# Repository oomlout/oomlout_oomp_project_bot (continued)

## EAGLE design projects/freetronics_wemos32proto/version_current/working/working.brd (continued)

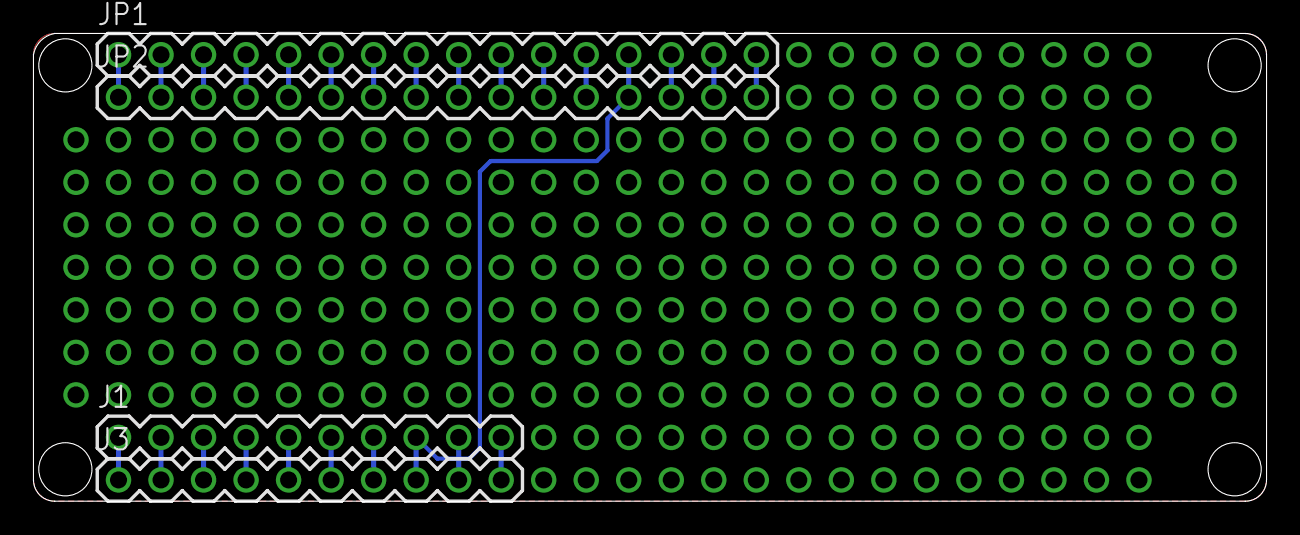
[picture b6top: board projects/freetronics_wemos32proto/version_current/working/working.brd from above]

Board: 2 copper layers, 73.7 x 27.9 mm, 4 parts (0 on the bottom side), 23 nets.

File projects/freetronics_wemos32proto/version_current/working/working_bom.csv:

"Id";"Designator";"Footprint";"Quantity";"Designation";"Supplier and ref";
1;"JP1,JP2";"1X16";2;"M16PTH";;;
2;"J1,J3";"1X10";2;"Digital_8_13";;;
3;"@HOLE0,@HOLE2,@HOLE3,@HOLE1";"";4;"";;;
